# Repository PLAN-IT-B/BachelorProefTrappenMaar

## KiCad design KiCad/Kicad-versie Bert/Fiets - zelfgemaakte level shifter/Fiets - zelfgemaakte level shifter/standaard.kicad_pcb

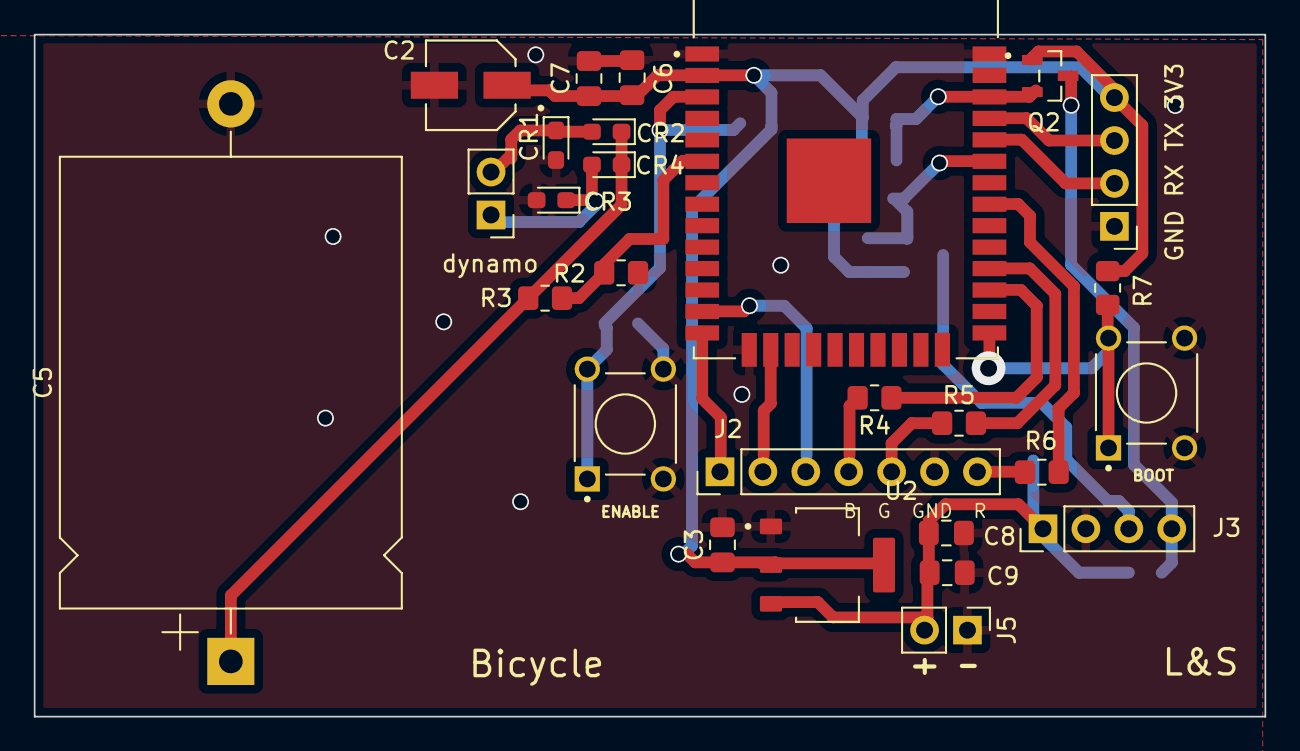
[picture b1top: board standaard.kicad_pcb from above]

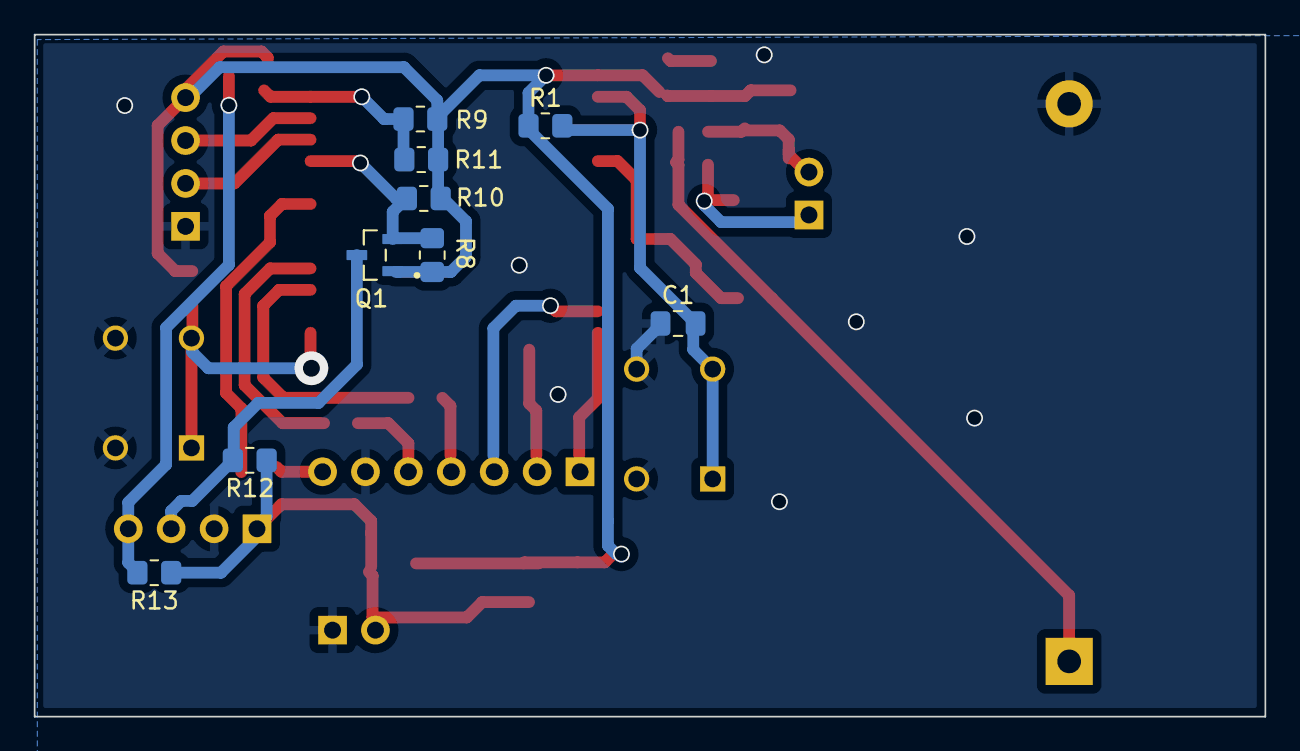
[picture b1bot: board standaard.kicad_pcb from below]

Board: 2 copper layers, 72.8 x 40.4 mm, 36 parts (9 on the bottom side), 24 nets.

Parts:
C1: 1u; C_0805_2012Metric_Pad1.18x1.45mm_HandSolder
C2: 220u; CAP_EEE0JA101WR
C3: 22u; C_0805_2012Metric_Pad1.18x1.45mm_HandSolder
C5: 1000µ; CP_Axial_L26.5mm_D20.0mm_P33.00mm_Horizontal
C6, C8: 0.1u; C_0805_2012Metric_Pad1.18x1.45mm_HandSolder
C7, C9: 4.7u; C_0805_2012Metric_Pad1.18x1.45mm_HandSolder
CR1, CR2, CR3, CR4: 1N4148W-TP; D_0603_1608Metric_Pad1.05x0.95mm_HandSolder
J1: Conn_01x04_Female; PinHeader_1x04_P2.54mm_Vertical
J2: Conn_01x07_Male; PinHeader_1x07_P2.54mm_Vertical
J3: 282837-4; PinHeader_1x04_P2.54mm_Vertical
J4, J5: 282841-2; PinHeader_1x02_P2.54mm_Vertical
Q1, Q2: 2N7002; SOT95P240X111-3N
R1, R7, R8, R9, R10, R11, R12, R13: 10k; R_0805_2012Metric_Pad1.20x1.40mm_HandSolder
R2: 120; R_0805_2012Metric_Pad1.20x1.40mm_HandSolder
R3: 560; R_0805_2012Metric_Pad1.20x1.40mm_HandSolder
R4, R5, R6: 82; R_0805_2012Metric_Pad1.20x1.40mm_HandSolder
SW1: ENABLE; SW_1825910-6-4
SW2: BOOT; SW_1825910-6-4
U1: ESP32-WROOM-32E_(16MB); MODULE_ESP32-WROOM-32(8MB)
U2: AMS1117; SOT229P700X180-4N

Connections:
+3V3: C2.1, C3.1, C6.1, C7.1, J1.4, Q1.1, Q2.1, R1.1, R7.1, R8.1, R9.1, R10.1, R11.1, U1.2 (3V3), U2.2 (VOUT), U2.4 (VOUT)
GND: C1.1, C2.2, C3.2, C5.2, C6.2, C7.2, C8.1, C9.2, CR1.2, CR3.2, J1.1, J2.6, J3.2, J5.1, R2.1, SW1.3, SW1.4, SW2.3, SW2.4, U1.1 (GND), U1.15 (GND), U1.38 (GND), U2.1 (ADJ/GND)
unnamed: C1.2, R1.2, SW1.1, SW1.2, U1.3 (EN)
unnamed: C5.1, CR2.1, CR4.1, R3.2
unnamed: C8.2, C9.1, J3.1, J5.2, R12.1, R13.1, U2.3 (VIN)
unnamed: CR1.1, CR2.2, J4.2
unnamed: CR3.1, CR4.2, J4.1
unnamed: J1.2, U1.34 (RXD0)
unnamed: J1.3, U1.35 (TXD0)
unnamed: J2.1, U1.14 (IO12)
unnamed: J2.2, U1.16 (IO13)
unnamed: J2.3, U1.13 (IO14)
unnamed: J2.4, R4.2
unnamed: J2.5, R5.2
unnamed: J2.7, R6.2
unnamed: J3.3, Q1.3, R12.2
unnamed: J3.4, Q2.3, R13.2
unnamed: Q1.2, R8.2, R10.2, U1.33 (IO21)
unnamed: Q2.2, R9.2, R11.2, U1.36 (IO22)
unnamed: R2.2, R3.1, U1.6 (IO34)
unnamed: R4.1, U1.27 (IO16)
unnamed: R5.1, U1.28 (IO17)
unnamed: R6.1, U1.31 (IO19)
unnamed: R7.2, SW2.1, SW2.2, U1.25 (IO0)

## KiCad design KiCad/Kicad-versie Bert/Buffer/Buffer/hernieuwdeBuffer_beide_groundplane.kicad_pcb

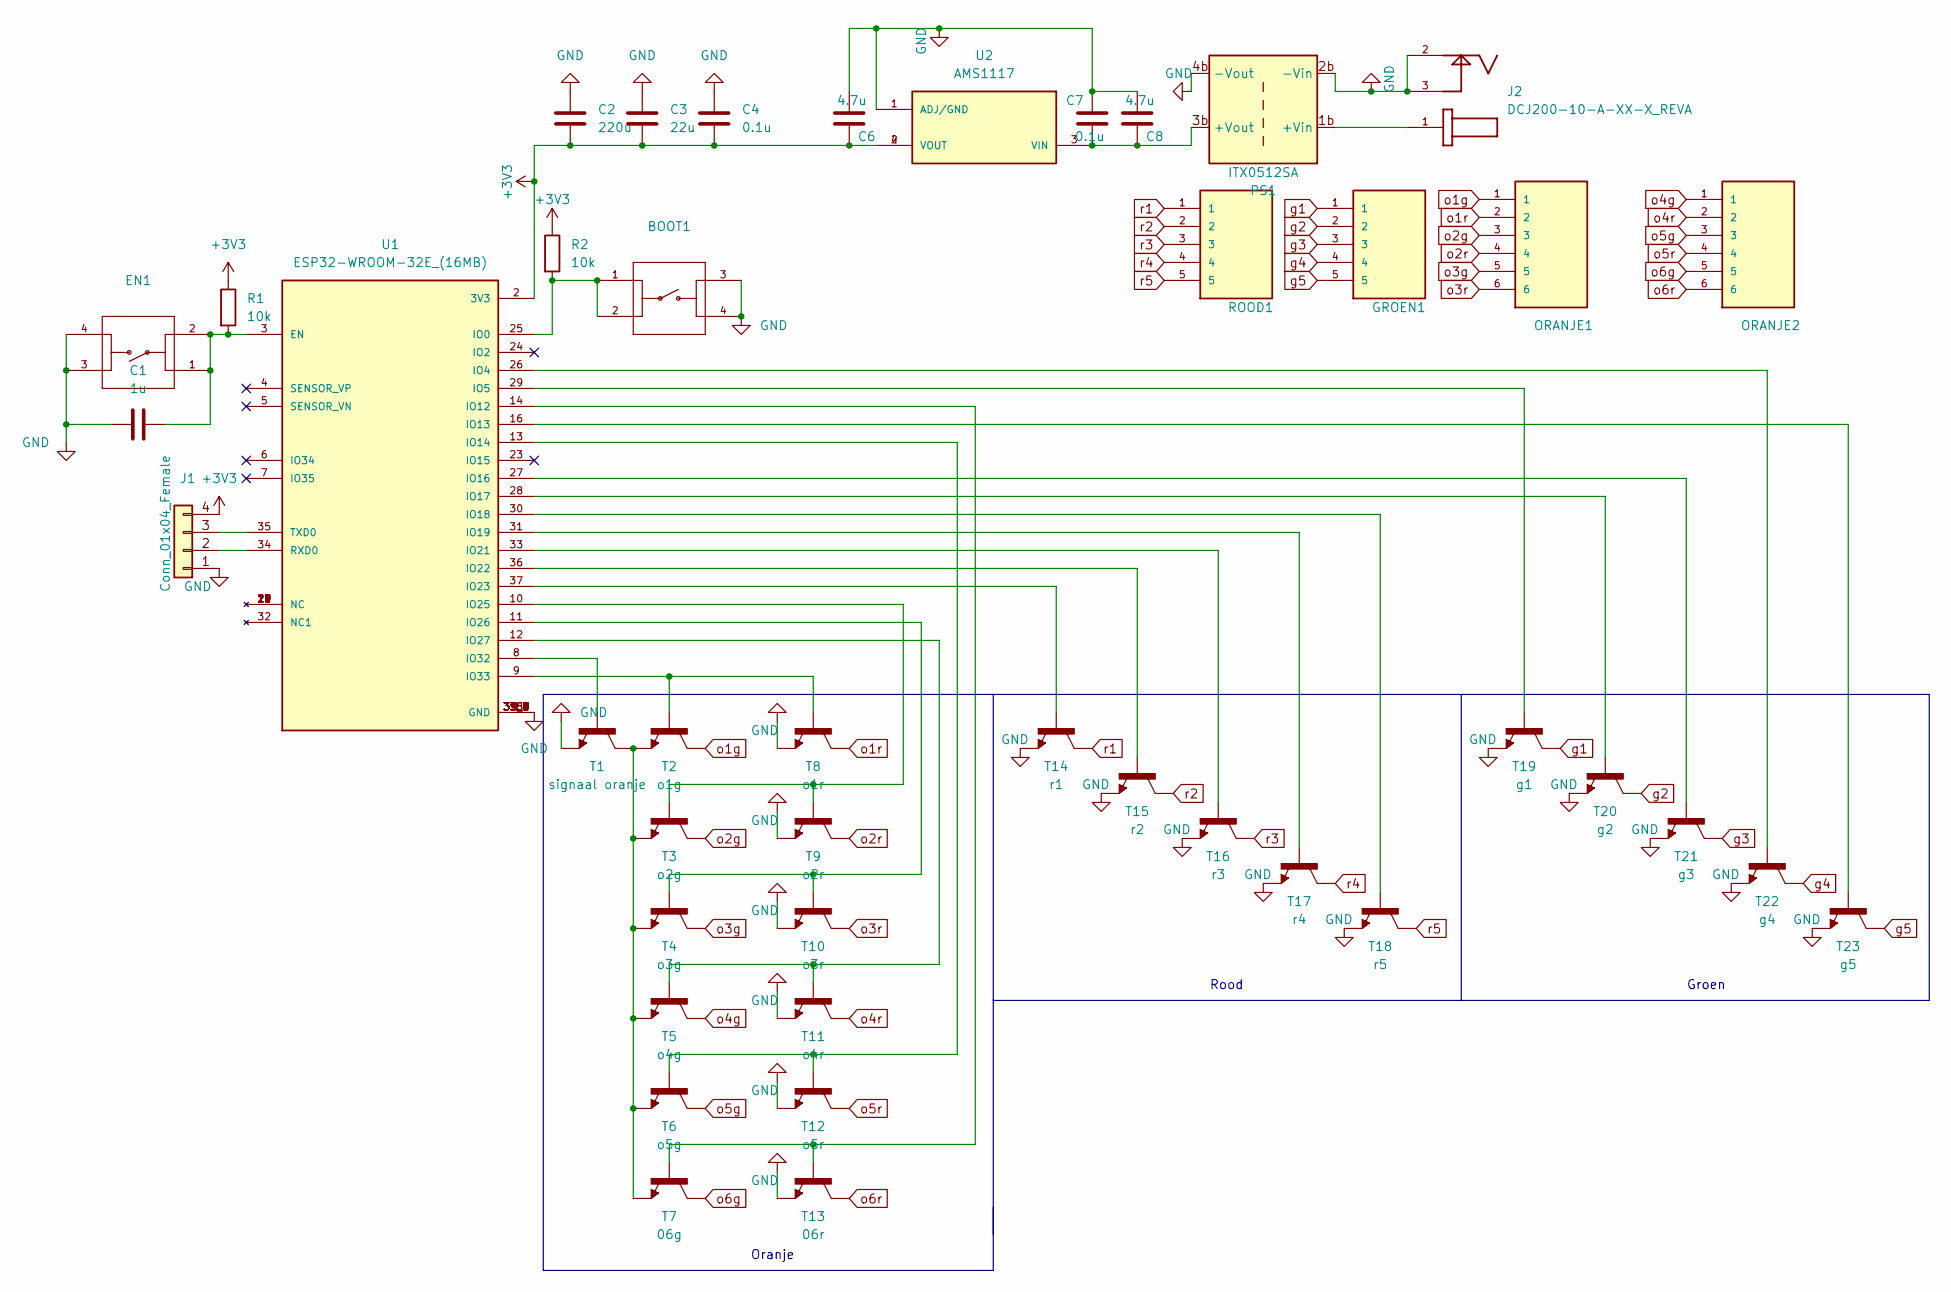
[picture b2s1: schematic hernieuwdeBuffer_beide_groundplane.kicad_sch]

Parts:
BOOT1: (no value)
C1: 1u; C_0805_2012Metric
C2: 220u; CAP_EEE0JA101WR
C3: 22u; C_0805_2012Metric
C4, C7: 0.1u; C_0805_2012Metric
C6, C8: 4.7u; C_0805_2012Metric
EN1: (no value)
GROEN1: (no value)
J1: Conn_01x04_Female; PinHeader_1x04_P2.54mm_Vertical
J2: DCJ200-10-A-XX-X_REVA; GCT_DCJ200-10-A-XX-X_REVA
ORANJE1, ORANJE2: (no value)
PS1: ITX0512SA; Buck Converter
R1, R2: 10k; R_0805_2012Metric
ROOD1: (no value)
T1: signaal oranje; SOT23
T2: o1g; SOT23
T3: o2g; SOT23
T4: o3g; SOT23
T5: o4g; SOT23
T6: o5g; SOT23
T7: 06g; SOT23
T8: o1r; SOT23
T9: o2r; SOT23
T10: o3r; SOT23
T11: o4r; SOT23
T12: o5r; SOT23
T13: 06r; SOT23
T14: r1; SOT23
T15: r2; SOT23
T16: r3; SOT23
T17: r4; SOT23
T18: r5; SOT23
T19: g1; SOT23
T20: g2; SOT23
T21: g3; SOT23
T22: g4; SOT23
T23: g5; SOT23
U1: ESP32-WROOM-32E_(16MB); XCVR_ESP32-WROOM-32E_(16MB); PARTREV 1.4
U2: AMS1117; SOT229P700X180-4N; PARTREV N/A

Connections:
+3V3: C2.1, C3.1, C4.1, C6.1, J1.4, R1.1, R2.1, U1.2 (3V3), U2.2 (VOUT), U2.4 (VOUT)
GND: BOOT1.3, BOOT1.4, C1.1, C2.2, C3.2, C4.2, C6.2, C7.1, C8.2, EN1.3, EN1.4, J1.1, J2.2, J2.3, PS1.2b (-Vin), PS1.4b (-Vout), T1.2, T8.2, T9.2, T10.2, T11.2, T12.2, T13.2, T14.2, T15.2, T16.2, T17.2, T18.2, T19.2, T20.2, T21.2, T22.2, T23.2, U1.1 (GND), U1.15 (GND), U1.38 (GND), U1.39_1 (GND), U1.39_2 (GND), U1.39_3 (GND), U1.39_4 (GND), U1.39_5 (GND), U1.39_6 (GND), U1.39_7 (GND), U1.39_8 (GND), U1.39_9 (GND), U2.1 (ADJ/GND)
unnamed: C1.2, EN1.1, EN1.2, R1.2, U1.3 (EN)
unnamed: C7.2, C8.1, PS1.3b (+Vout), U2.3 (VIN)
unnamed: J1.2, U1.34 (RXD0)
unnamed: J1.3, U1.35 (TXD0)
unnamed: J2.1, PS1.1b (+Vin)
unnamed: BOOT1.1, BOOT1.2, R2.2, U1.25 (IO0)
unnamed: T1.1, U1.8 (IO32)
unnamed: T1.3, T2.2, T3.2, T4.2, T5.2, T6.2, T7.2
unnamed: T2.1, T8.1, U1.9 (IO33)
unnamed: T3.1, T9.1, U1.10 (IO25)
unnamed: T4.1, T10.1, U1.11 (IO26)
unnamed: T5.1, T11.1, U1.12 (IO27)
unnamed: T6.1, T12.1, U1.13 (IO14)
unnamed: T7.1, T13.1, U1.14 (IO12)
unnamed: T14.1, U1.37 (IO23)
unnamed: T15.1, U1.36 (IO22)
unnamed: T16.1, U1.33 (IO21)
unnamed: T17.1, U1.31 (IO19)
unnamed: T18.1, U1.30 (IO18)
unnamed: T19.1, U1.29 (IO5)
unnamed: T20.1, U1.28 (IO17)
unnamed: T21.1, U1.27 (IO16)
unnamed: T22.1, U1.26 (IO4)
unnamed: T23.1, U1.16 (IO13)
g1: GROEN1.1, T19.3
g2: GROEN1.2, T20.3
g3: GROEN1.3, T21.3
g4: GROEN1.4, T22.3
g5: GROEN1.5, T23.3
o1g: ORANJE1.1, T2.3
o1r: ORANJE1.2, T8.3
o2g: ORANJE1.3, T3.3
o2r: ORANJE1.4, T9.3
o3g: ORANJE1.5, T4.3
o3r: ORANJE1.6, T10.3
o4g: ORANJE2.1, T5.3
o4r: ORANJE2.2, T11.3
o5g: ORANJE2.3, T6.3
o5r: ORANJE2.4, T12.3
o6g: ORANJE2.5, T7.3
o6r: ORANJE2.6, T13.3
r1: ROOD1.1, T14.3
r2: ROOD1.2, T15.3
r3: ROOD1.3, T16.3
r4: ROOD1.4, T17.3
r5: ROOD1.5, T18.3

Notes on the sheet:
Oranje
Groen
Rood

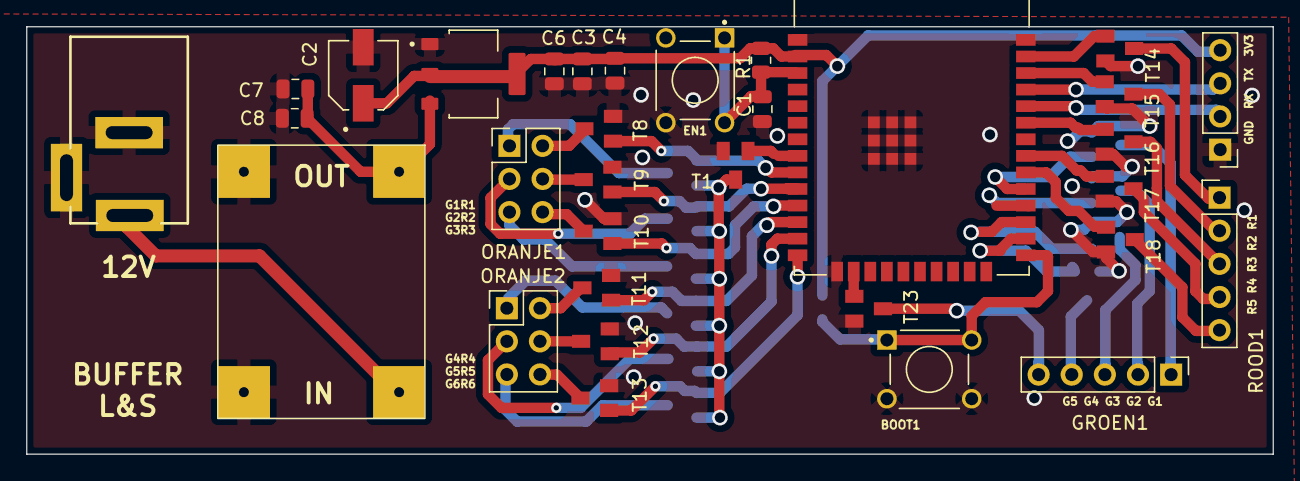
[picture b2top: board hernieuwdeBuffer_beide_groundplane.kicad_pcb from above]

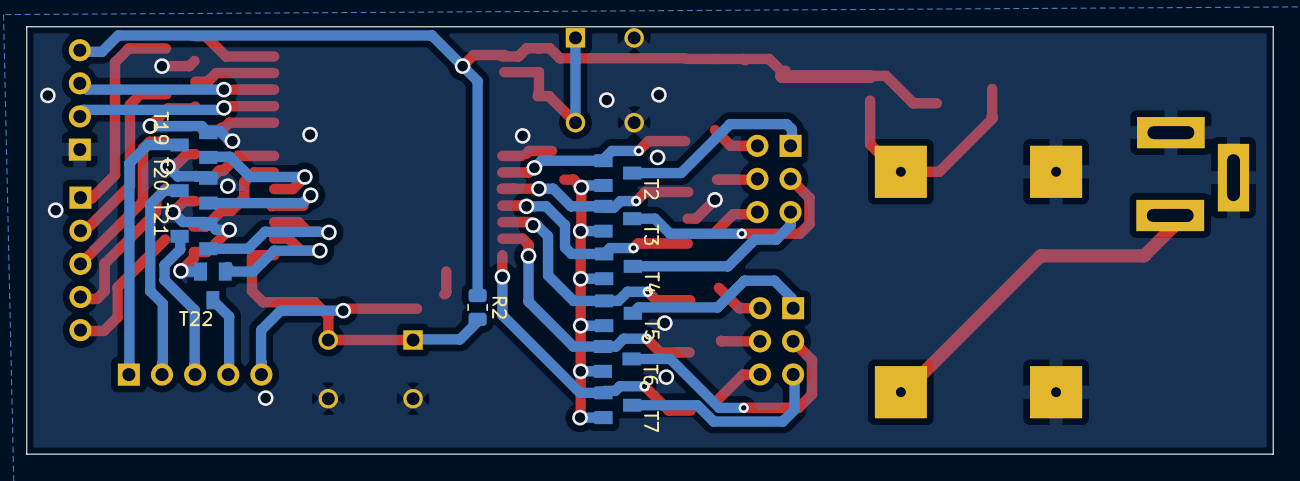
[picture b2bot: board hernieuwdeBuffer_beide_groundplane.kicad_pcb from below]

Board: 2 copper layers, 95.6 x 32.8 mm, 43 parts (11 on the bottom side), 48 nets.

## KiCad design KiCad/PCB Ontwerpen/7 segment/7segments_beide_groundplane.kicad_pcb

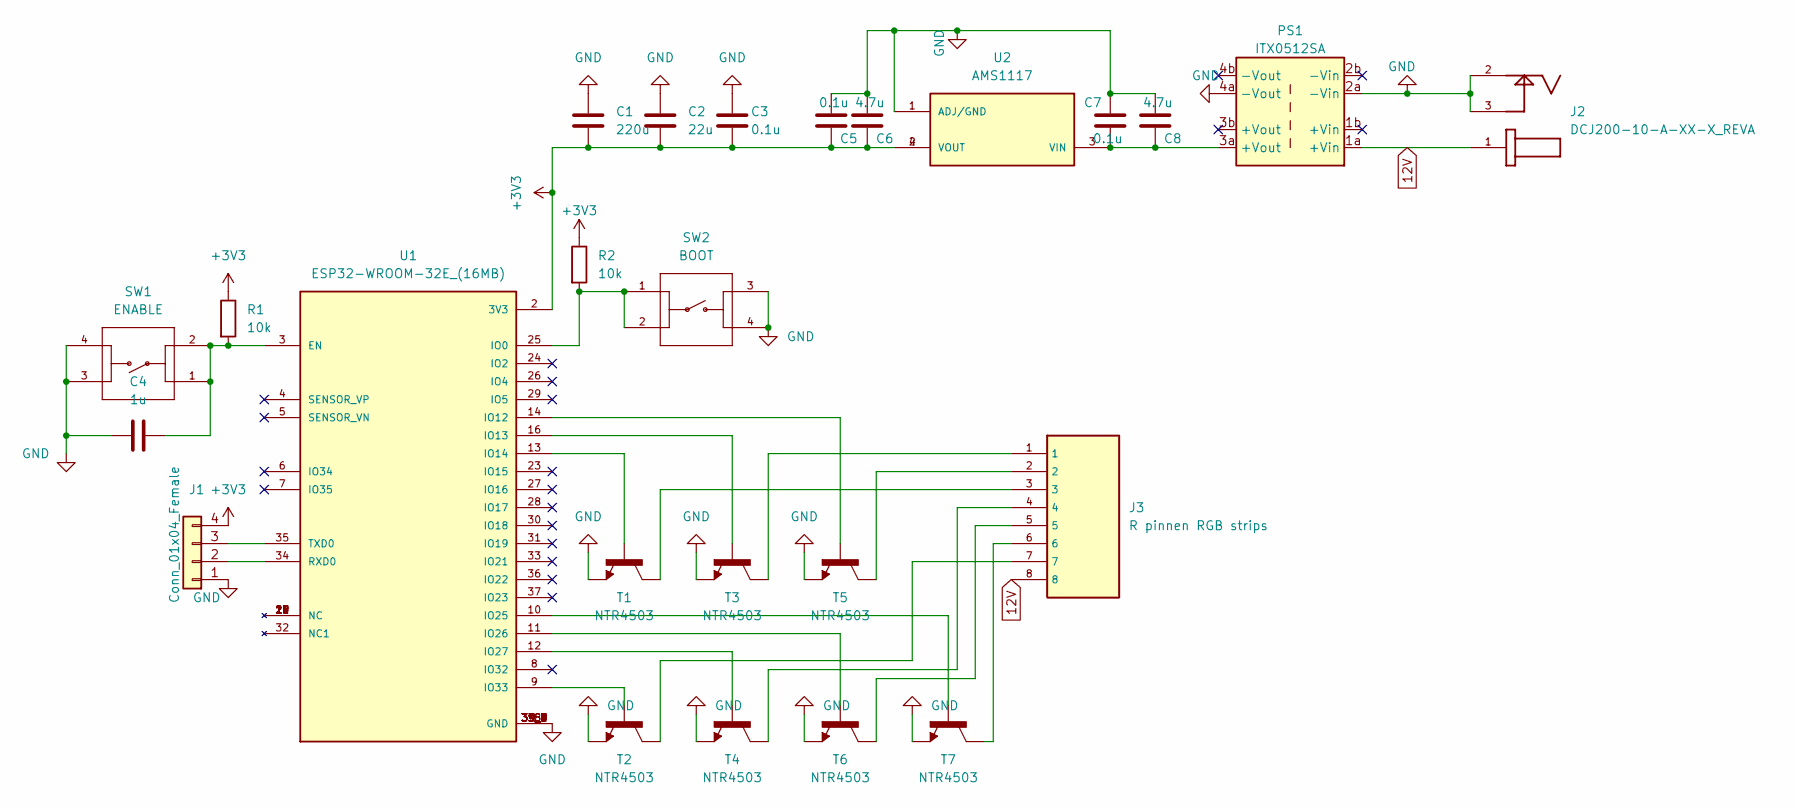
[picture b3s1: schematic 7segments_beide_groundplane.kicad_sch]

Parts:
C1: 220u; CAP_EEE0JA101WR
C2: 22u; C_0805_2012Metric
C3, C5, C7: 0.1u; C_0805_2012Metric
C4: 1u; C_0805_2012Metric
C6, C8: 4.7u; C_0805_2012Metric
J1: Conn_01x04_Female; PinHeader_1x04_P2.54mm_Vertical
J2: DCJ200-10-A-XX-X_REVA; GCT_DCJ200-10-A-XX-X_REVA
J3: R pinnen RGB strips; TE_1546215-8
PS1: ITX0512SA; Buck Converter
R1, R2: 10k; R_0805_2012Metric
SW1: ENABLE; SW_1825910-6-4
SW2: BOOT; SW_1825910-6-4
T1, T2, T3, T4, T5, T6, T7: NTR4503; SOT23
U1: ESP32-WROOM-32E_(16MB); XCVR_ESP32-WROOM-32E_(16MB); PARTREV 1.4
U2: AMS1117; SOT229P700X180-4N; PARTREV N/A

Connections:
12V: J2.1, J3.8, PS1.1a (+Vin)
+3V3: C1.1, C2.1, C3.1, C5.1, C6.1, J1.4, R1.1, R2.1, U1.2 (3V3), U2.2 (VOUT), U2.4 (VOUT)
GND: C1.2, C2.2, C3.2, C4.1, C5.2, C6.2, C7.1, C8.2, J1.1, J2.2, J2.3, PS1.2a (-Vin), PS1.4a (-Vout), SW1.3, SW1.4, SW2.3, SW2.4, T1.2, T2.2, T3.2, T4.2, T5.2, T6.2, T7.2, U1.1 (GND), U1.15 (GND), U1.38 (GND), U1.39_1 (GND), U1.39_2 (GND), U1.39_3 (GND), U1.39_4 (GND), U1.39_5 (GND), U1.39_6 (GND), U1.39_7 (GND), U1.39_8 (GND), U1.39_9 (GND), U2.1 (ADJ/GND)
unnamed: C4.2, R1.2, SW1.1, SW1.2, U1.3 (EN)
unnamed: C7.2, C8.1, PS1.3a (+Vout), U2.3 (VIN)
unnamed: J1.2, U1.34 (RXD0)
unnamed: J1.3, U1.35 (TXD0)
unnamed: J3.1, T3.3
unnamed: J3.2, T5.3
unnamed: J3.3, T1.3
unnamed: J3.4, T4.3
unnamed: J3.5, T6.3
unnamed: J3.6, T7.3
unnamed: J3.7, T2.3
unnamed: R2.2, SW2.1, SW2.2, U1.25 (IO0)
unnamed: T1.1, U1.13 (IO14)
unnamed: T2.1, U1.9 (IO33)
unnamed: T3.1, U1.16 (IO13)
unnamed: T4.1, U1.12 (IO27)
unnamed: T5.1, U1.14 (IO12)
unnamed: T6.1, U1.11 (IO26)
unnamed: T7.1, U1.10 (IO25)

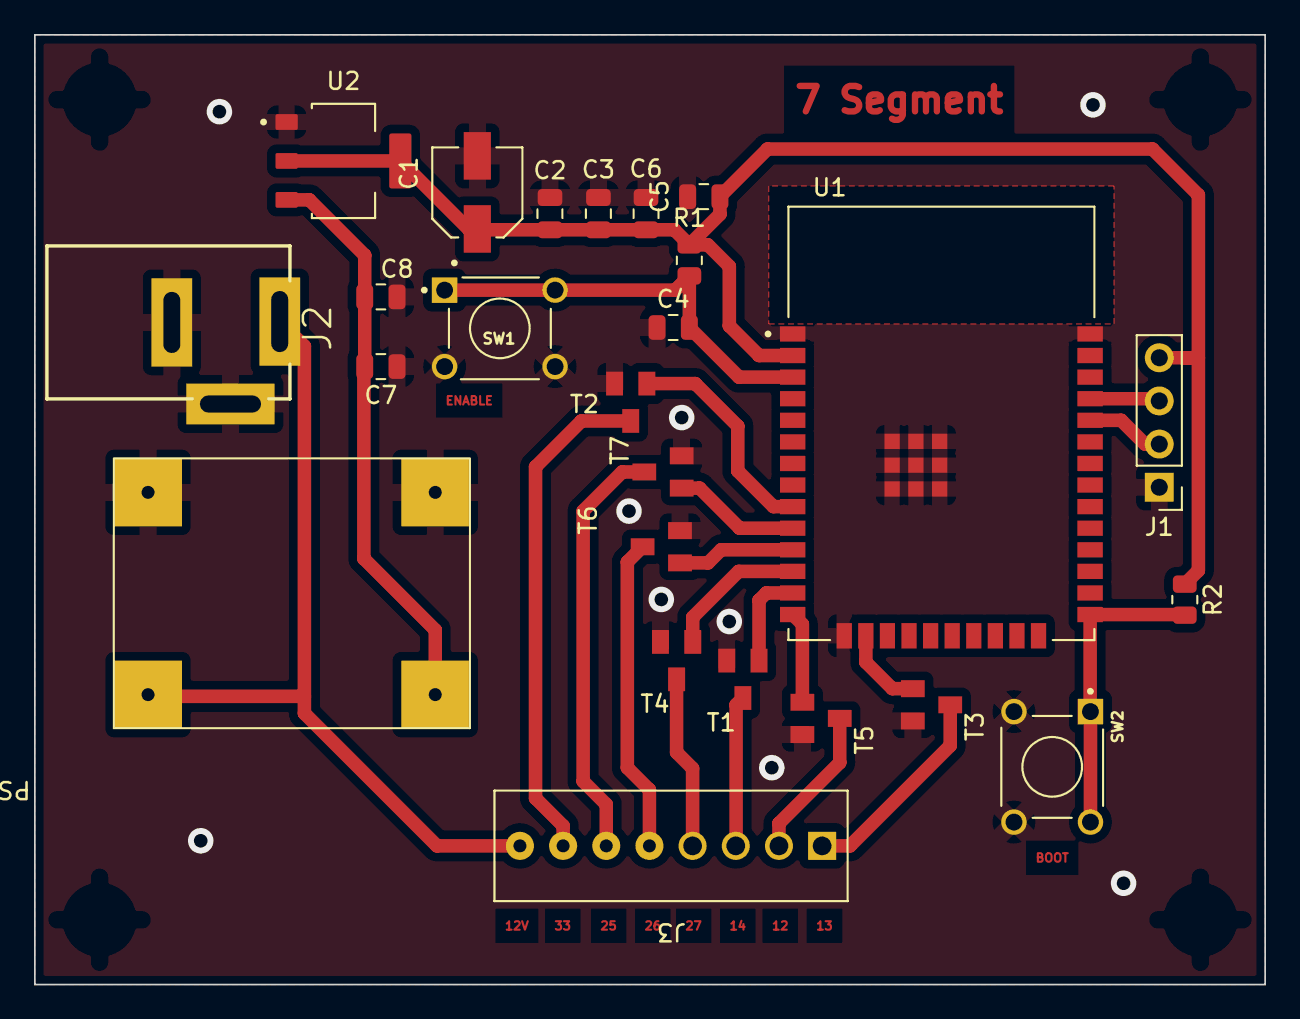
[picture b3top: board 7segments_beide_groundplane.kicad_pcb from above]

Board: 2 copper layers, 72.4 x 55.9 mm, 25 parts (0 on the bottom side), 22 nets.

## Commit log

2022-02-16 Reed Relay
    begin van reed relay code met lcd
2022-02-21 blokschema's trappen maar
    Begin flowcharts waarin de stappen worden beschreven die de esp's doorlopen
2022-02-21 creatie van gantt chart
    gant chart zonder kleuren maar wel in pdf vorm
2022-02-21 Update gedrag centrale ESP trappen maar.pdf
    reset functie toegevoegd aan flowchart voor wanneer de bandjes worden afgenomen, zodat de buffer helemaal leeg loopt
2022-02-21 Create Implementatie.docx
    in deze file wordt de implementatie uitgelegd met de basiselementen die we nodig hebben om de puzzel te realiseren
2022-02-22 toevoeging blacklight aan flowchart
2022-02-22 sukkelen om te uploaden, niks veranderd
2022-02-26 begin BOM
    Hierin staat voornamelijk de BOM voor de puzzel zelf en de buffer, het deel over de bijkomende puzzel werd hier nog niet in opgenomen
2022-02-27 Add files via upload
    1e versie ReedSwitch (om te testen)
2022-02-27 Bemerkingen/ideeën BOM
2022-02-28 overlezen en verdere aanvullingen
    benodigdheden 7 segment display toegevoegd
2022-03-01 Create BOM.xlsx
    BOM in Excel
2022-03-01 update bom met link naar websites
2022-03-01 communicatie tussen 2 esp's proberen verwezenlijken
    nog niet geslaagd
2022-03-08 toevoeging 2e bestelling
    blacklight voor fietsgenerator
2022-03-08 nieuwe werkwijze om snelheid af te leiden
    overstappen naar spanningsdeler op fietsdynamo zodat we de spanning kunnen doorsturen naar een esp32 (ipv reed relay)
2022-03-08 toevoeging snelheid aflezen via esp
    werken met een gelijkrichter en spanningsdeler zodat spanning over weerstand kan doorgestuurd worden naar esp en zijn ingebouwde adc
2022-03-08 CodeSnelheidsmeting
2022-03-08 code sender communication between esps
2022-03-08 communicatie tussen esps
    deze map bevat enkel de juiste code voor de receiver
2022-03-08 updates van libraries
    ging automatisch, ik heb zelf niks veranderd
2022-03-08 versie sender lyssa
2022-03-08 Verplaatsing (onafgewerkte code)
    onafgewerkte code ->testzone
    afgewerkte code -> code
2022-03-08 verplaatste code
    onafgewerkte code -> testzone
    afgewerkte code -> codes
2022-03-21 automatische library updates
2022-03-21 Sender en receiver
2022-03-21 aanpassing buffer
2022-03-22 Code met communicatie buffer
2022-03-22 aanpassingen code
2022-03-22 functies uiteen halen
    aparte functie maken voor het versturen naar 7 segment
2022-03-22 aanpassing code
2022-03-28 goed begin voor buffer met rood, geel/oranje en groen
    Het geel/oranje werkt met een ledcWrite maar die functie bevat een delay voor groen, die nog niet helemaal op punt staat
2022-03-28 Problemen zoeken met senden en receiven
2022-03-28 sender en receiver 7 segment
2022-03-28 buffer rgb driver
2022-03-29 aanapassingen
2022-04-01 aanpassingen
    in mapjes gestoken
2022-04-02 ontwerpen van pcb ontwerp voor de 7 segment displays
2022-04-02 hernoemen map
2022-04-02 aanpassingen
    alles in mapjes steken
2022-04-02 aanpassen naam
2022-04-03 automatische library-updates
2022-04-03 update standaard kicad schema
2022-04-03 kicad fiets
2022-04-03 aanpassingen fiets Kicad
2022-04-03 kicad drawings
2022-04-03 laatste aanpassingen Fiets Kicad (+voeding)
2022-04-04 aanpassingen
2022-04-04 kicad
2022-04-04 updates standaard schema
2022-04-05 aanpassingen
    aanpass kicad fiets
2022-04-05 kicad aanpassingen buffer
2022-04-07 update buffer
    enkel schema van de buffer is volledig in orde met LDO!!!
2022-04-07 aanpassingen fiets (fouten eruit, ground plane, lijnen dikker)
2022-04-07 betere versie kicad fiets
2022-04-09 7segments aangepast naar correcte versie (kicad)
2022-04-09 laatste aanpassingen kicad 7segment
2022-04-09 aanpass kicad
2022-04-09 updaten van 7 segment ground plane(s)
    versie voor 7 segment met 1 ground plane aan achterkant en andere versie met ground plane aan voor- en achterkant
2022-04-11 aanpassingen aan kicad ontwerpen van 7segment en buffer
    toevoeging van groundplanes
2022-04-11 cut-outs groundplanes onder antenne
    enkel voor 7 segments en buffer
2022-04-11 aanmaak BOM 2e bestelronde
2022-04-12 aanpassingen 11/04 kicad
2022-04-12 update rgbdriver voor testen mosfets
2022-04-12 kicad fiets hertekend
2022-04-12 testcode voor enkele ledstrip geel licht
2022-04-12 updates kroonsteentjes naar 2.54mm voor 7segment en buffer
2022-04-13 aanpassingen kicad fiets
2022-04-13 fiets hermaakt (2 versies level shifter)
2022-04-14 aanmaak mapje voor finale ontwerpen
2022-04-14 aanpassingen fiets
2022-04-14 definitieve ontwerpen in map PCB ontwerpen geplaatst
2022-04-14 laatste aanpassingen aan pcb ontwerpen
2022-04-14 kopiëren van juiste pcb naar mapje over buffer
2022-04-14 aanpass
2022-04-14 aanpassing 7 segment naar dc jack
2022-04-19 kicad versie bert
2022-04-19 assembly voor boxes en back-up code
2022-04-19 aanpassingen code buffer leds
2022-04-19 code buffer met leds buffer
2022-04-19 solid works 7 segments
    juist gat voor kabel ontbreekt
2022-04-19 in mapjes steken
2022-04-26 box fiets
2022-04-26 gat en dxf files 7 segments
    gat toegevoegd voor voeding 7 segments en aanmaak dxf files voor het laser cutten
2022-04-26 ruimte vrijmaken op github en kleine aanpassing 7 segments solidworks
2022-04-27 svg bestanden voor laser cutten
2022-04-28 laser cut files voor kleinere 7 segment en bovenkant fiets
2022-04-28 aangepaste bovenkant voor fiets
    nu zijn het de juiste afmetingen voor het lcd scherm
2022-05-01 svg bestand aangepast voor fiets
2022-05-02 test your buddy + 7 segment led tester
2022-05-02 aanpassingen laatste week
2022-05-03 behuizing buffer voor lasercutten
2022-05-06 code opgekuist en werkende
2022-05-09 aanpassing laatste boxen naar 3mm karton
2022-05-11 testcode buffer
    kleuren oplopend
2022-05-12 website map
2022-05-12 png to jpg
2022-05-12 foto eeschema fiets
2022-05-13 aanpassingen led tester 7 segment
2022-05-13 goed code toevoegen, fotos website, ...
2022-05-13 code verplaatsen + fotos toevoegen
2022-05-15 aanpassingen aan eeschema en pcb fiets
    spanningsdeler gewijzigd en condensator juist georiënteerd
2022-05-15 fotos website
2022-05-15 flowchart
2022-05-15 BOM final
2022-05-16 fotos gereduceert formaat
2022-05-18 code aanpassing volle buffer
2022-05-19 codo aanpassing
2022-05-20 fotos van componenten
2022-05-20 code segmenten in 1 mapje gestoken
2022-05-23 fotos voor presentatie
2022-05-24 foto uv lamp

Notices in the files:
parts and their libraries:
COPYRIGHT: Copyright (C) 2018 Accelerated Designs. All rights reserved
